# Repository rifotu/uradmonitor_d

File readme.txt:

Portable Environmental Monitor
(C) 2015 Radu Motisan , radu.motisan@gmail.com

Released under lGPL v3.

http://www.pocketmagic.net/portable-environmental-monitor/

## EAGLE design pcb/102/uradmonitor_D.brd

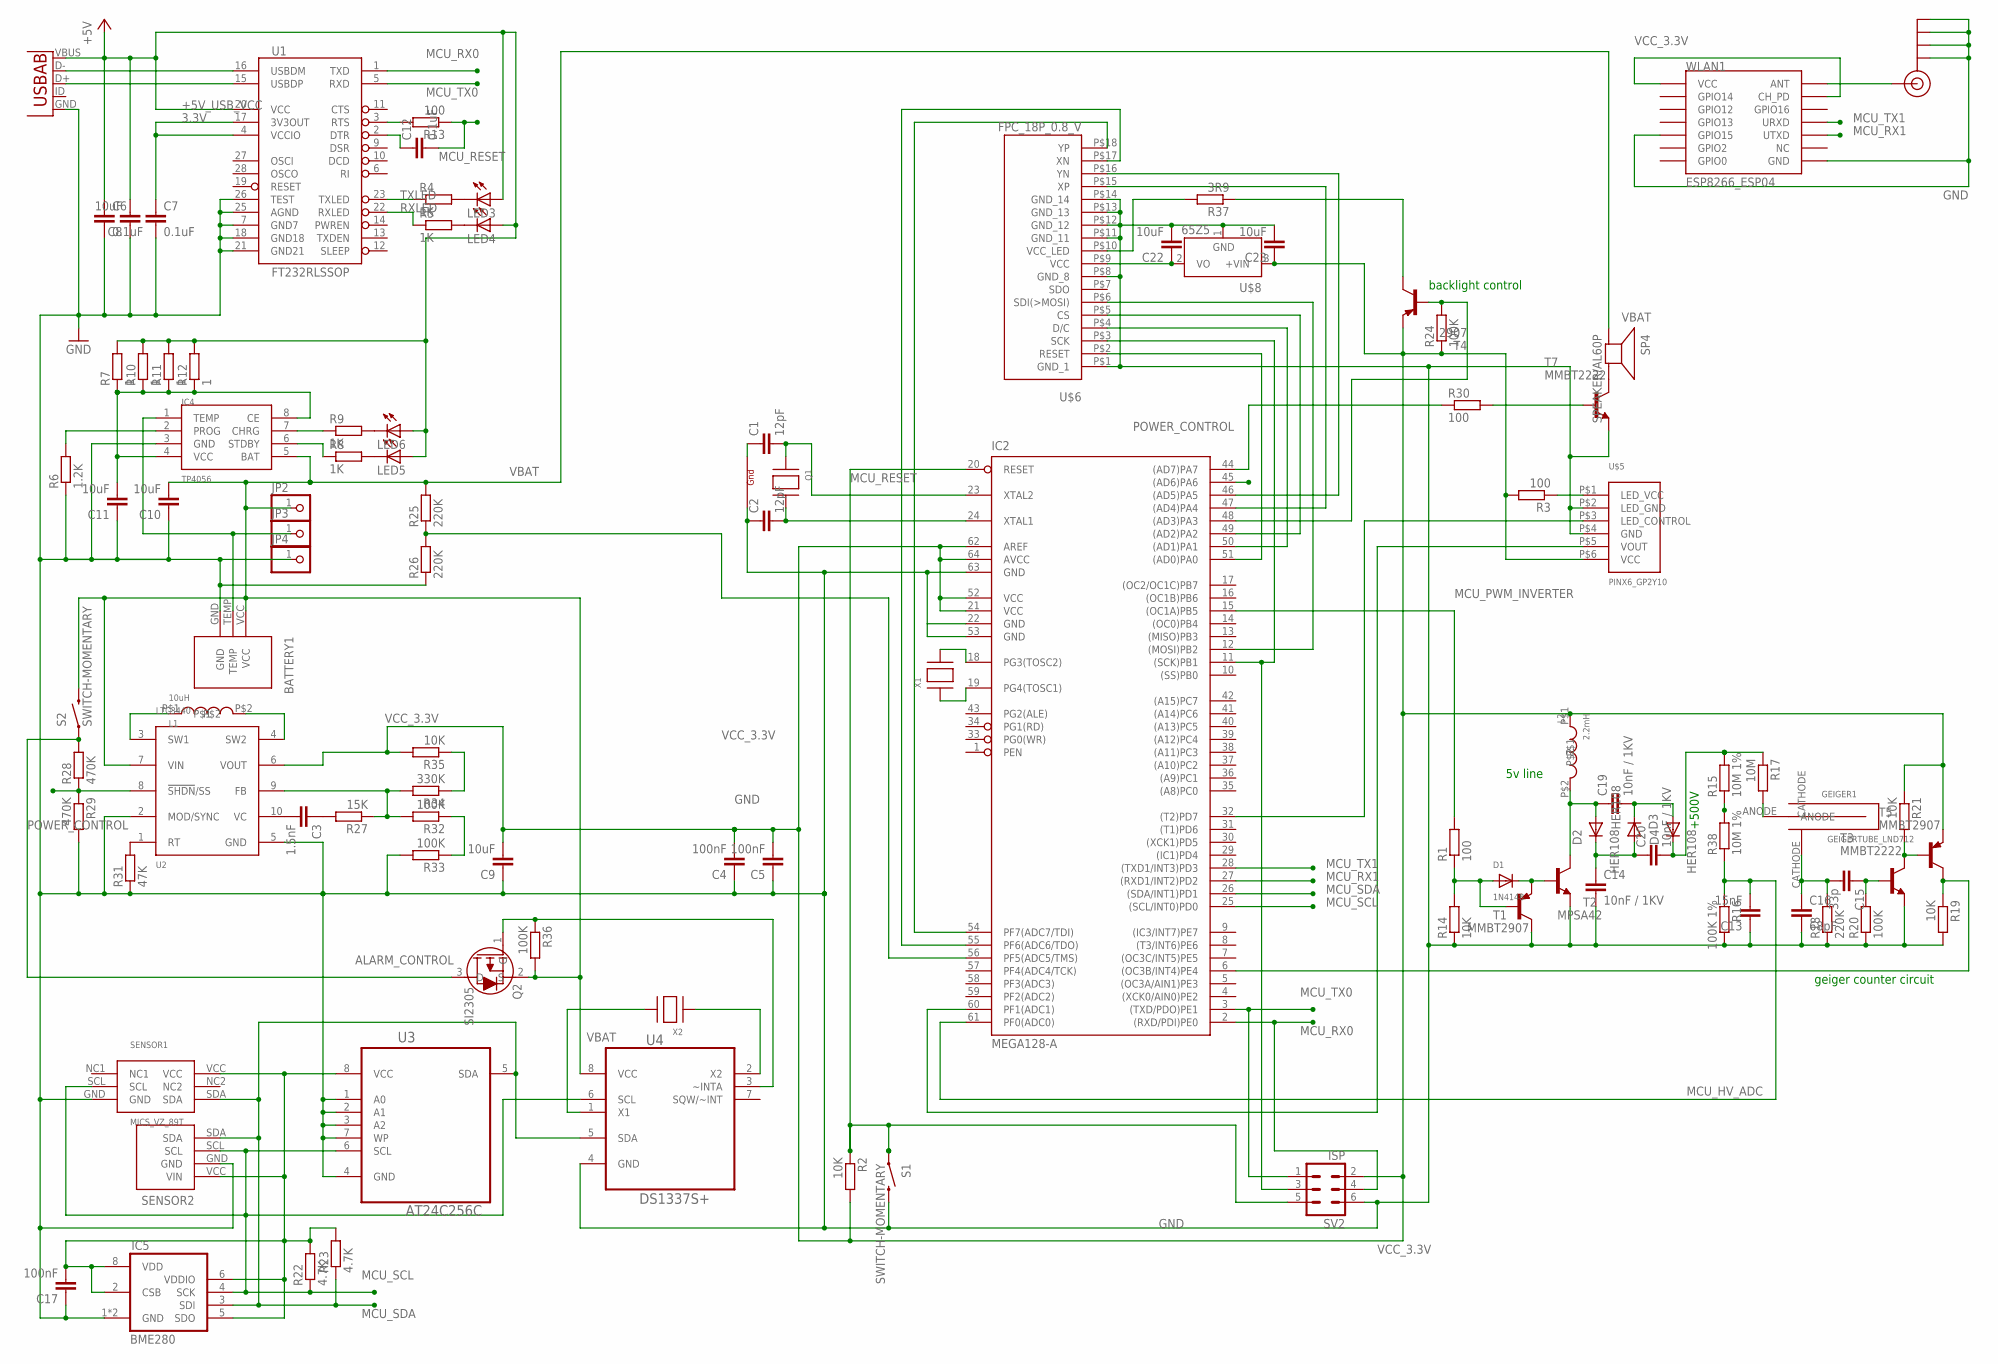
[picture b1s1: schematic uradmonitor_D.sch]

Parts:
BATTERY1: BAT-CASIO-NP40BATTERY; BAT-CASIO-NP40
C1, C2: 12pF; C0805K
C3: 1.5nF; C0805K
C4, C5, C17: 100nF; C0805K
C6, C7, C12: 0.1uF; 0805
C8, C9, C10, C11: 10uF; C0805K
C13: 15nF; C0805K
C14, C19, C20: 10nF / 1KV; C1206K
C15: 33p; C0805K
C16: 68pF; C0805K
C22, C23: 10uF; C0805
D1: 1N4148; SOD-323F
D2, D3, D4: HER108; DO-214AC
GEIGER1: GEIGERTUBE_LND712
IC2: MEGA128-A; TQFP64
IC4: TP4056
IC5: BME280
J$1: SMA_EDGE; SMA-EDGE
JP2, JP3, JP4: PINHD-1X1CB; 1X01-CLEANBIG
L1: 10uH; DO1608
L2: 2.2mH; DO1608
LED3, LED4: LEDCHIP-LED0805; CHIP-LED0805
LED5, LED6: LED3MM
Q1: XTAL-4-3225; NX3225
Q2: SI2305; SOT23
R1, R3, R13, R30: 100; R0805
R2, R14, R19, R21, R35: 10K; R0805
R4, R5, R8, R9: 1K; R0805
R6: 1.2K; R0805
R7, R10, R11, R12: 1; R0805
R15, R38: 10M 1%; 0204/7
R16: 100K 1%; R0805
R17: 10M; 0204/7
R18: 220K; 0204/7
R20, R24, R32, R33, R36: 100K; R0805
R22, R23: 4.7K; R0805
R25, R26: 220K; R0805
R27: 15K; R0805
R28, R29: 470K; R0805
R31: 47K; R0805
R34: 330K; R0805
R37: 3R9; R0805
S1: SWITCH-MOMENTARY; TACTILE-SWITCH-1101NE
S2: SWITCH-MOMENTARY; TACTILE-PTH-SIDEEZ
SENSOR1: MICS_VZ_89T
SENSOR2: BMP180; SENSOR_GY68
SP4: SPEAKER/AL60P; AL60P
SV2: ISP; MA03-2
T1, T5: MMBT2907; SOT23-BEC
T2: MPSA42; SOT23-BEC
T3, T7: MMBT2222; SOT23-BEC
T4: 2907; SOT23-BEC
U1: FT232RLSSOP; SSOP28DB
U2: LTC3440; MSOP-10
U3: AT24C256C; SOIC127P600X175-8N
U4: DS1337S+; SOIC127P600X175-8N
U$2: USB_AB; USB-AB-MICRO-SMD
U$5: PINX6_GP2Y10
U$6: FPC_18P_0.8_V
U$8: 65Z5; SOT23
WLAN1: ESP8266_ESP04
X1, X2: XTAL-3.2X1.5; XTAL3215

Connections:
3.3V: C7.1, U1.4 (VCCIO), U1.17 (3V3OUT)
+5V_USB_VCC: C6.1, C8.2, LED3.A, LED4.A, LED5.A, LED6.A, R7.2, R10.2, R11.2, R12.2, U1.20 (VCC), U$2.VBUS
ALARM_CONTROL: Q2.3 (D), R28.2, S2.1
GND: BATTERY1.GND, C2.1, C4.1, C5.1, C6.2, C7.2, C8.1, C9.1, C10.1, C11.1, C13.1, C14.2, C16.2, C17.1, C22.2, C23.2, IC2.22 (GND), IC2.53 (GND), IC2.63 (GND), IC4.3 (GND), IC5.1 (GND), IC5.7 (GND), J$1.GND@0 (GND), J$1.GND@1 (GND), J$1.GND@2 (GND), J$1.GND@3 (GND), JP4.1, Q1.2 (G2), R6.1, R14.1, R16.2, R18.1, R19.2, R20.1, R26.1, R29.2, R31.1, R33.2, S1.P$2 (2), SENSOR1.GND, SENSOR2.GND, SV2.6, T1.C, T2.E, T3.E, T7.E, U1.7 (GND7), U1.18 (GND18), U1.21 (GND21), U1.25 (AGND), U1.26 (TEST), U2.2 (MOD/SYNC), U2.5 (GND), U3.1 (A0), U3.2 (A1), U3.3 (A2), U3.4 (GND), U3.7 (WP), U4.4 (GND), U$2.GND, U$5.P$2 (LED_GND), U$5.P$4 (GND), U$6.P$1 (GND_1), U$6.P$8 (GND_8), U$6.P$11 (GND_11), U$6.P$12 (GND_12), U$6.P$13 (GND_13), U$6.P$14 (GND_14), U$8.1 (GND), WLAN1.GND, WLAN1.GPIO15
MCU_HV_ADC: C13.2, IC2.61 (PF0(ADC0)), R16.1, R38.1
MCU_INT4: IC2.6 ((OC3B/INT4)PE4), R19.1, T5.C
MCU_PWM_INVERTER: IC2.15 ((OC1A)PB5), R1.2
MCU_RESET: C12.2, IC2.20 (RESET), R2.1, R13.1, S1.P$1 (1), SV2.5
MCU_RX0: IC2.2 ((RXD/PDI)PE0), SV2.4, U1.1 (TXD)
MCU_RX1: IC2.27 ((RXD1/INT2)PD2), WLAN1.UTXD
MCU_SCL: IC2.25 ((SCL/INT0)PD0), IC5.4 (SCK), R22.1, SENSOR1.SCL, SENSOR2.SCL, U3.6 (SCL), U4.6 (SCL)
MCU_SDA: IC2.26 ((SDA/INT1)PD1), IC5.3 (SDI), R23.1, SENSOR1.SDA, SENSOR2.SDA, U3.5 (SDA), U4.5 (SDA)
MCU_TX0: IC2.3 ((TXD/PDO)PE1), SV2.1, U1.5 (RXD)
MCU_TX1: IC2.28 ((TXD1/INT3)PD3), WLAN1.URXD
unnamed: J$1.SIG (SIGNAL), WLAN1.ANT
unnamed: LED3.C, R4.2
unnamed: IC2.56 (PF5(ADC5/TMS)), R25.1, R26.2
unnamed: L1.P$2, U2.4 (SW2)
unnamed: R3.1, U$5.P$1 (LED_VCC)
unnamed: IC2.11 ((SCK)PB1), SV2.3, U$6.P$3 (SCK)
unnamed: LED4.C, R5.2
unnamed: D1.A, R1.1, R14.2, T1.B
unnamed: C1.2, IC2.23 (XTAL2), Q1.1 (X1)
unnamed: L1.P$1, U2.3 (SW1)
unnamed: C2.2, IC2.24 (XTAL1), Q1.3 (X2)
unnamed: IC2.18 (PG3(TOSC2)), X1.P$2
unnamed: R37.1, T4.C
unnamed: IC2.12 ((MOSI)PB2), U$6.P$6 (SDI(>MOSI))
unnamed: U1.16 (USBDM), U$2.D-
unnamed: U1.15 (USBDP), U$2.D+
unnamed: D1.C, T1.E, T2.B
unnamed: IC4.6 (STDBY), R8.1
unnamed: GEIGER1.ANODE, R17.2
unnamed: C15.1, R20.2, T3.B
unnamed: IC4.7 (CHRG), R9.1
unnamed: LED6.K (C), R9.2
unnamed: IC2.32 ((T2)PD7), U$5.P$3 (LED_CONTROL)
unnamed: LED5.K (C), R8.2
unnamed: C12.1, U1.2 (DTR)
unnamed: IC4.2 (PROG), R6.2
unnamed: R13.2, U1.3 (RTS)
unnamed: C11.2, IC4.4 (VCC), IC4.8 (CE), R7.1, R10.1, R11.1, R12.1
unnamed: IC2.19 (PG4(TOSC1)), X1.P$1
unnamed: BATTERY1.TEMP, IC4.1 (TEMP), JP3.1
unnamed: IC2.60 (PF1(ADC1)), U$5.P$5 (VOUT)
unnamed: IC2.44 ((AD7)PA7), R30.1
unnamed: R31.2, U2.1 (RT)
unnamed: C14.1, C20.1, D2.C, D3.A
unnamed: IC2.51 ((AD0)PA0), U$6.P$2 (RESET)
unnamed: C3.2, U2.10 (VC)
unnamed: IC2.50 ((AD1)PA1), U$6.P$4 (D/C)
unnamed: IC2.49 ((AD2)PA2), U$6.P$5 (CS)
unnamed: IC2.47 ((AD4)PA4), U$6.P$15 (XP)
unnamed: IC2.46 ((AD5)PA5), U$6.P$16 (YN)
unnamed: C15.2, C16.1, GEIGER1.CATHODE, R18.2
unnamed: IC2.54 (PF7(ADC7/TDI)), U$6.P$18 (YP)
unnamed: IC2.55 (PF6(ADC6/TDO)), U$6.P$17 (XN)
unnamed: IC2.48 ((AD3)PA3), R24.2, T4.B
unnamed: C3.1, R27.2
unnamed: R27.1, R32.2, R34.2, U2.9 (FB)
unnamed: R32.1, R33.1
unnamed: R34.1, R35.1
unnamed: C19.1, D2.A, L2.P$2, T2.C
unnamed: C22.1, U$6.P$9 (VCC), U$8.2 (VO)
unnamed: C19.2, D3.C, D4.A
unnamed: C20.2, D4.C, R15.2, R17.1
unnamed: U4.2 (X2), X2.P$1
unnamed: U4.1 (X1), X2.P$2
unnamed: R30.2, T7.B
unnamed: R21.2, T3.C, T5.B
unnamed: R15.1, R38.2
unnamed: Q2.1 (G), R36.1, U4.3 (~INTA)
unnamed: C1.1, Q1.4 (G1)
unnamed: R37.2, U$6.P$10 (VCC_LED)
POWER_CONTROL: IC2.45 ((AD6)PA6), R28.1, R29.1, U2.8 (!SHDN!/SS)
RXLED: R5.1, U1.22 (RXLED)
SOLDER_TUBE: SP4.2 (-), T7.C
TXLED: R4.1, U1.23 (TXLED)
VBAT: BATTERY1.VCC, C10.2, IC4.5 (BAT), JP2.1, Q2.2 (S), R25.2, R36.2, S2.2, SP4.1 (+), U2.7 (VIN), U4.8 (VCC)
VCC_3.3V: C4.2, C5.2, C9.2, C17.2, C23.1, IC2.21 (VCC), IC2.52 (VCC), IC2.62 (AREF), IC2.64 (AVCC), IC5.2 (CSB), IC5.5 (SDO), IC5.6 (VDDIO), IC5.8 (VDD), L2.P$1, R2.2, R3.2, R21.1, R22.2, R23.2, R24.1, R35.2, SENSOR1.VCC, SENSOR2.VCC (VIN), SV2.2, T4.E, T5.E, U2.6 (VOUT), U3.8 (VCC), U$5.P$6 (VCC), U$8.3 (+VIN), WLAN1.CH_PD, WLAN1.VCC

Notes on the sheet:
5v line
+500V
geiger counter circuit
backlight control

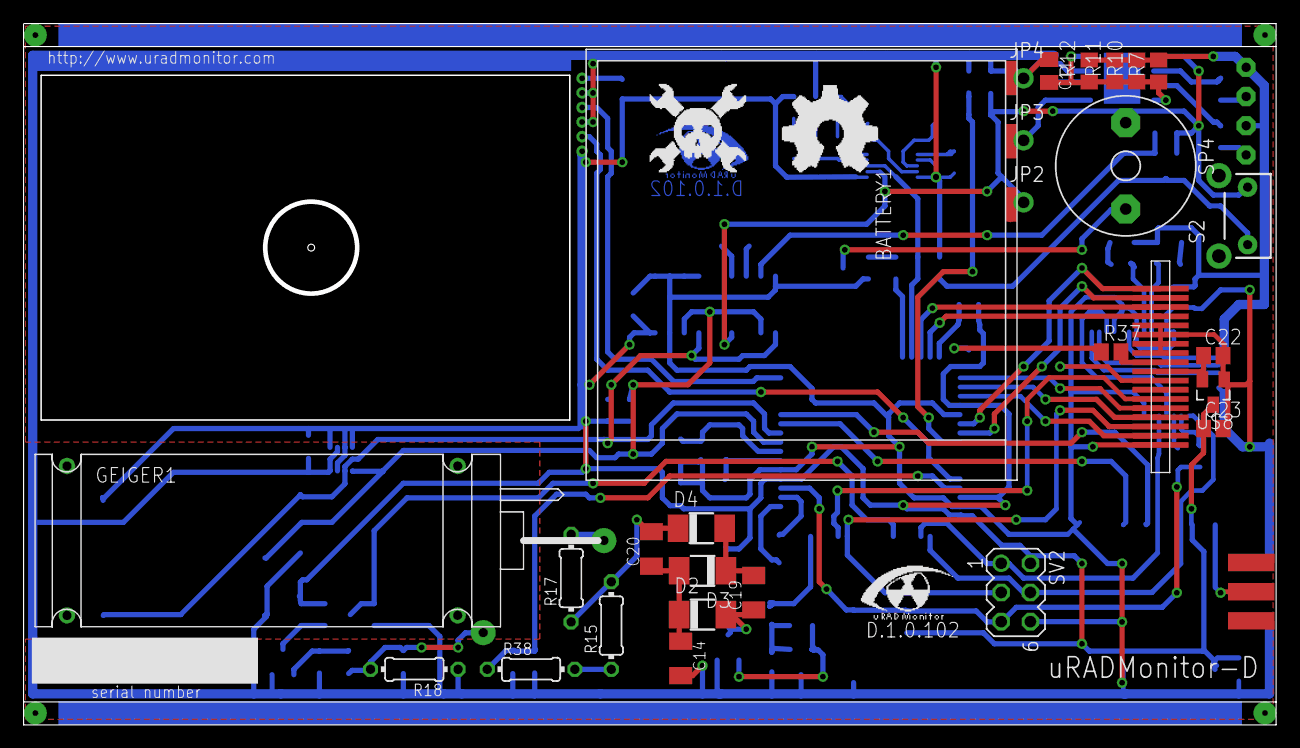
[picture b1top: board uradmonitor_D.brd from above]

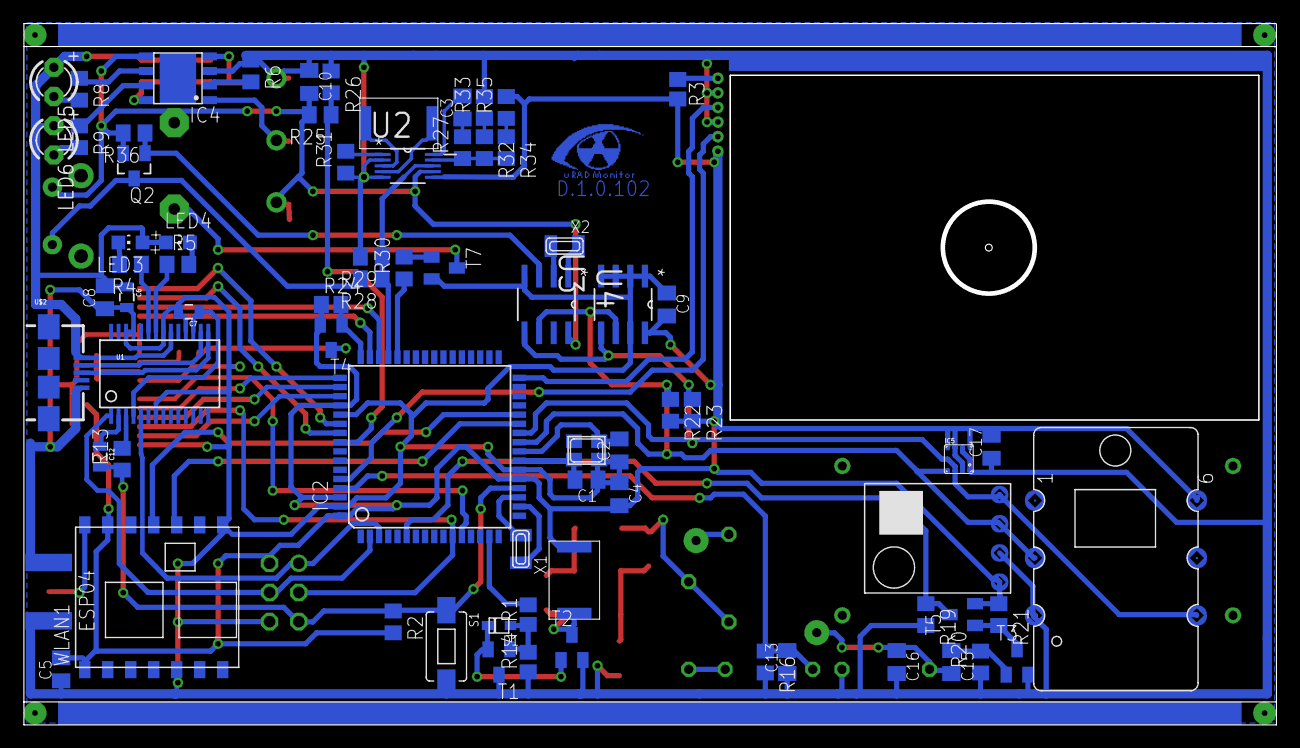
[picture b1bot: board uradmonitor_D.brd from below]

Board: 2 copper layers, 108.7 x 60.7 mm, 103 parts (73 on the bottom side), 80 nets.

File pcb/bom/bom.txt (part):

Partlist

Exported from uradmonitor_D.101.sch at 14/08/15 00:19

EAGLE Version 6.1.0 Copyright (c) 1988-2012 CadSoft

Assembly variant: 

Part     Value                         Device                        Package               Library                    Sheet

BATTERY1 BAT-CASIO-NP40BATTERY         BAT-CASIO-NP40BATTERY         BAT-CASIO-NP40        uradmonitor                1
C1       33p                           C-EUC0805K                    C0805K                rcl                        1
C2       33p                           C-EUC0805K                    C0805K                rcl                        1
C3       10uF                          C-EUC0805K                    C0805K                rcl                        1
C4       100nF                         C-EUC0805K                    C0805K                rcl                        1
C5       100nF                         C-EUC0805K                    C0805K                rcl                        1
C6       0.1uF                         CAP0805                       0805                  SparkFun                   1
C7       0.1uF                         CAP0805                       0805                  SparkFun                   1
C8       10uF                          C-EUC0805K                    C0805K                rcl                        1
C9       100nF                         C-EUC0805K                    C0805K                rcl                        1
C10      10uF                          C-EUC0805K                    C0805K                rcl                        1
C11      10uF                          C-EUC0805K                    C0805K                rcl                        1
C12      0.1uF                         CAP0805                       0805                  SparkFun                   1
C13      15nF                          C-EUC0805K                    C0805K                rcl                        1
C14      10nF / 1KV                    C-EU050-025X075               C050-025X075          rcl                        1
C15      33p                           C-EUC0805K                    C0805K                rcl                        1
C16      68pF                          C-EUC0805K                    C0805K                rcl                        1
C17      100nF                         C-EUC0805K                    C0805K                rcl                        1
C18      10uF                          C-EUC0805K                    C0805K                rcl                        1
D1       1N4148                        DIODESOD-323F                 SOD-323F              adafruit                   1
D2       HER108                        DIODE-DO-214AC                DO-214AC              diode                      1
D3       1N581-SMA                     1N581-SMA                     SMA-DIODE             digital-toy                1
GEIGER1  GEIGERTUBE_LND712             GEIGERTUBE_LND712             GEIGERTUBE_LND712     uradmonitor                1
IC2      MEGA128-A                     MEGA128-A                     TQFP64                atmel                      1
IC3      REG1117                       REG1117                       SOT223                burr-brown                 1
IC4      TP4056                        TP4056                        TP4056                uradmonitor                1
IC5      BME280                        BME280                        BME280                uradmonitor                1
J$1      SMA_EDGE                      SMA_EDGE                      SMA-EDGE              sparkfun-connectors        1
JP1                                    PINHD-1X3                     1X03                  adafruit                   1
JP3      Dust Sensor                   PINHD-1X6CB                   1X06-CLEANBIG         adafruit                   1
LED3                                   LEDCHIP-LED0805               CHIP-LED0805          adafruit                   1
LED4                                   LEDCHIP-LED0805               CHIP-LED0805          adafruit                   1
LED5                                   LED3MM                        LED3MM                adafruit                   1
LED6                                   LED3MM                        LED3MM                adafruit                   1
Q1       8Mhz                          XTAL/S                        QS                    special                    1
Q2                                     CRYSTALTC26H                  TC26H                 adafruit                   1
Q4       SI2305                        SI2305                        SOT23                 uradmonitor                1
R1       100                           R-EU_R0805                    R0805                 resistor                   1
R2       10K                           R-EU_R0805                    R0805                 rcl                        1
R3       100                           R-EU_R0805                    R0805                 resistor                   1
R4       1K                            R-EU_R0805                    R0805                 rcl                        1
R5       1K                            R-EU_R0805                    R0805                 rcl                        1
R6       1.2K                          R-EU_R0805                    R0805                 rcl                        1
R7       1                             R-EU_R0805                    R0805                 rcl                        1
R8       1K                            R-EU_R0805                    R0805                 rcl                        1
R9       1K                            R-EU_R0805                    R0805                 rcl                        1
R10      1                             R-EU_R0805                    R0805                 rcl                        1
R11      1                             R-EU_R0805                    R0805                 rcl                        1
R12      1                             R-EU_R0805                    R0805                 rcl                        1
R13      100                           R-EU_R0805                    R0805                 rcl                        1
R14      10K                           R-EU_R0805                    R0805                 resistor                   1
R15      10M 1%                        R-EU_0204/7                   0204/7                rcl                        1
R16      47K 1%                        R-EU_R0805                    R0805                 rcl                        1
R17      10M                           R-EU_0204/7                   0204/7                rcl                        1
R18      220K                          R-EU_0204/7                   0204/7                rcl                        1
R19      10K                           R-EU_R0805                    R0805                 rcl                        1
R20      100K                          R-EU_R0805                    R0805                 rcl                        1
R21      10K                           R-EU_R0805                    R0805                 rcl                        1
R22      4.7K                          R-EU_R0805                    R0805                 rcl                        1
R23      4.7K                          R-EU_R0805                    R0805                 rcl                        1
R24      100K                          R-EU_R0805                    R0805                 resistor                   1
R25      220K                          R-EU_R0805                    R0805                 rcl                        1
R26      220K                          R-EU_R0805                    R0805                 rcl                        1
R27      100K                          R-EU_R0805                    R0805                 rcl                        1
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
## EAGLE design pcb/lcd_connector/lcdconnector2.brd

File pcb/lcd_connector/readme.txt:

Only used prior to 1.0.102 hardware (also in beta release).

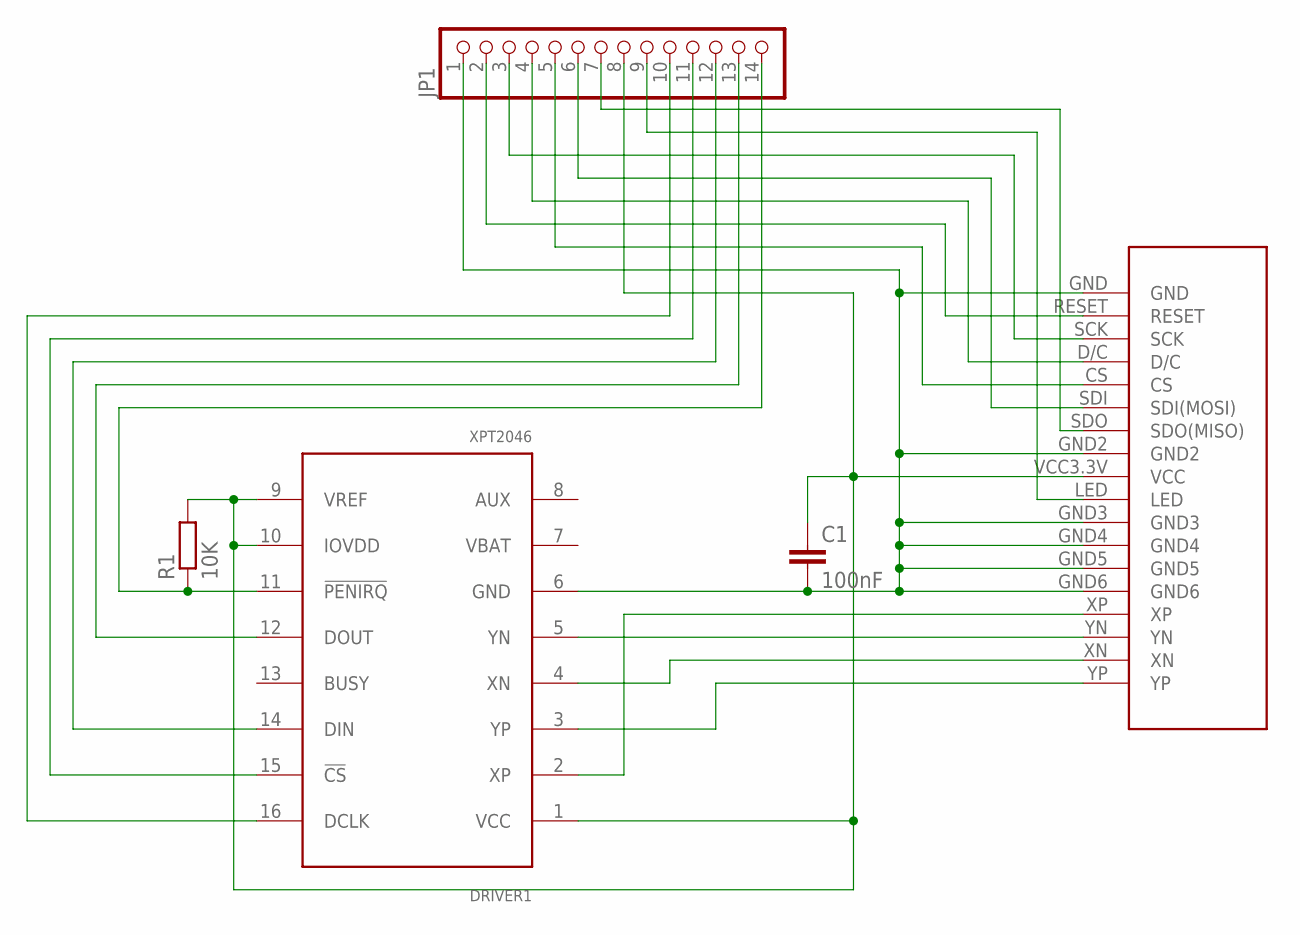
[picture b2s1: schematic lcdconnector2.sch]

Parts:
C1: 100nF; C0805K
CONNECTOR1: TJCTM24024-PINS
DRIVER1: XPT2046
JP1: PINHD-1X14-CB; 1X14-CB
R1: 10K; M0805

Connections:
unnamed: CONNECTOR1.XP, DRIVER1.2 (XP)
unnamed: CONNECTOR1.YP, DRIVER1.3 (YP)
unnamed: CONNECTOR1.XN, DRIVER1.4 (XN)
unnamed: CONNECTOR1.YN, DRIVER1.5 (YN)
unnamed: C1.2, CONNECTOR1.GND, CONNECTOR1.GND2, CONNECTOR1.GND3, CONNECTOR1.GND4, CONNECTOR1.GND5, CONNECTOR1.GND6, DRIVER1.6 (GND), JP1.1
unnamed: CONNECTOR1.CS, JP1.5
unnamed: CONNECTOR1.RESET, JP1.2
unnamed: CONNECTOR1.D/C, JP1.4
unnamed: CONNECTOR1.SDI (SDI(MOSI)), JP1.6
unnamed: CONNECTOR1.SCK, JP1.3
unnamed: CONNECTOR1.LED, JP1.9
unnamed: CONNECTOR1.SDO (SDO(MISO)), JP1.7
unnamed: DRIVER1.16 (DCLK), JP1.10
unnamed: DRIVER1.15 (!CS), JP1.11
unnamed: DRIVER1.14 (DIN), JP1.12
unnamed: DRIVER1.12 (DOUT), JP1.13
unnamed: DRIVER1.11 (!PENIRQ), JP1.14, R1.1
unnamed: C1.1, CONNECTOR1.VCC3.3V (VCC), DRIVER1.1 (VCC), DRIVER1.9 (VREF), DRIVER1.10 (IOVDD), JP1.8, R1.2

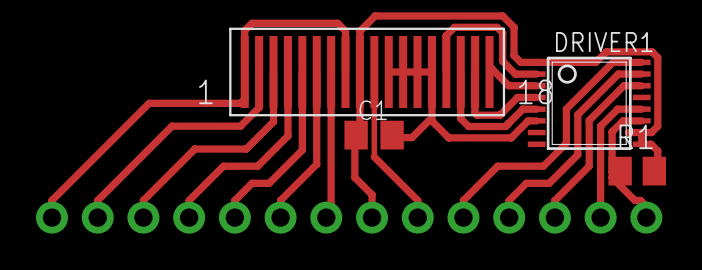
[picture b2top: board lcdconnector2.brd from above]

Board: 2 copper layers, 5 parts (0 on the bottom side), 18 nets.

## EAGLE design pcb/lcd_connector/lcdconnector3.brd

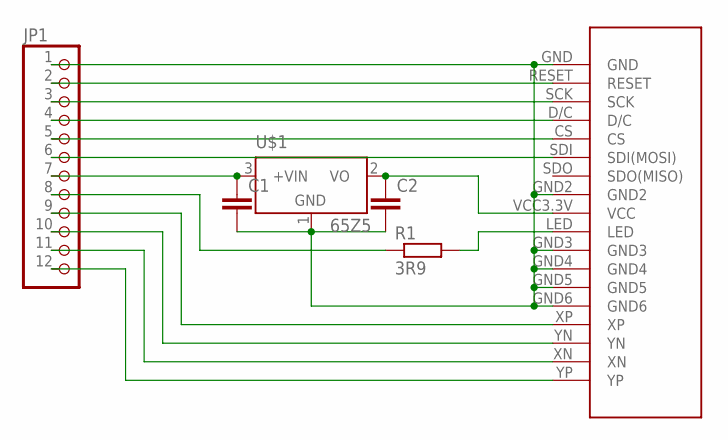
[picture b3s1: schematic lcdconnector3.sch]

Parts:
C1, C2: C-EUC0805; C0805
CONNECTOR1: TJCTM24024-PINS
JP1: PINHD-1X12-CB; 1X12-CB
R1: 3R9; R0805
U$1: 65Z5; SOT23

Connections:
unnamed: C1.2, C2.2, CONNECTOR1.GND, CONNECTOR1.GND2, CONNECTOR1.GND3, CONNECTOR1.GND4, CONNECTOR1.GND5, CONNECTOR1.GND6, JP1.1, U$1.1 (GND)
unnamed: CONNECTOR1.RESET, JP1.2
unnamed: CONNECTOR1.SCK, JP1.3
unnamed: CONNECTOR1.D/C, JP1.4
unnamed: CONNECTOR1.CS, JP1.5
unnamed: CONNECTOR1.SDI (SDI(MOSI)), JP1.6
unnamed: C1.1, JP1.7, U$1.3 (+VIN)
unnamed: C2.1, CONNECTOR1.VCC3.3V (VCC), U$1.2 (VO)
unnamed: CONNECTOR1.LED, R1.2
unnamed: JP1.8, R1.1
unnamed: CONNECTOR1.XP, JP1.9
unnamed: CONNECTOR1.YN, JP1.10
unnamed: CONNECTOR1.XN, JP1.11
unnamed: CONNECTOR1.YP, JP1.12

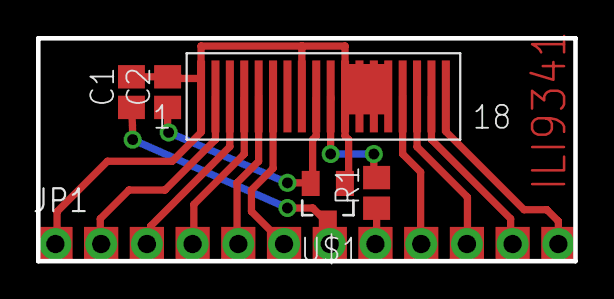
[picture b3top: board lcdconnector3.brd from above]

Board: 2 copper layers, 29.8 x 12.4 mm, 6 parts (0 on the bottom side), 14 nets.

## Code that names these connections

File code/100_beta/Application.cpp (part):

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
uint32_t 			deviceID 				= ((uint32_t) ((DEV_MODEL << 4) | DEV_RAD_DETECTOR) << 24) | ((uint32_t) DEV_ID);
// microcontroller pins
DigitalPin			lcdReset(&PORTA, PA0), lcdDC(&PORTA, PA1),  lcdCS(&PORTA, PA2), 							// LCD Pins
					lcdBacklight(&PORTA, PA3),																	// Backlight control, ON
					touchXP(&PORTA, PA4), touchYN(&PORTA, PA5), touchXN(&PORTF, PF6), touchYP(&PORTF, PF7), 	// touchscreen pins
					powerControl(&PORTA, PA6),																	// power control, OFF
					speaker(&PORTA, PA7),																		// speaker pin
					dustFlash(&PORTD, PD7, DigitalPin::OUTPUT, true);											// dust sensor control pin, ON
// various features
AsyncRTC128T0	 	time;										// handles the time interrupts
ADC10b				adc;										// 10bit ADC converter
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	// keep power pin High unless we want to shutdown
	powerControl = 1;

	// disable JTAG so we can use PF4,PF5,PF6,PF7 for ADC and GPIO
	MCUCSR |=(1<<JTD);MCUCSR |=(1<<JTD); // two times!!

	// init time RTC
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
	// init sensors
	bmp180.init();
	dust.init(&dustFlash, &adc, PF1);

	beep();
	// start UI
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
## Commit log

2015-08-13 beta release
2015-08-13 added bom for current diagram
2015-08-16 added gitignore
2015-08-16 git ignore in place
2015-08-19 enclosure v102
2015-08-19 gitignore for eagle temp files
2015-08-19 removed eagle temp files
2015-08-23 revision pcb 102. revision enclosure 103
2015-08-31 enclosure changes
2015-09-18 12pF caps to 16MHz crystal
2015-09-21 RC1 - mostly new GUI and Wifi

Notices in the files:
code/100_beta/Application.cpp:
Copyright (C) 2009 - 2015 Radu Motisan, radu.motisan@gmail.com
This project is free software; you can redistribute it and/or modify
it under the terms of the GNU Lesser General Public License as published
parts and their libraries:
sparkfun-connectors: Licensing: CC v3.0 Share-Alike You are welcome to use this library for commercial purposes.
